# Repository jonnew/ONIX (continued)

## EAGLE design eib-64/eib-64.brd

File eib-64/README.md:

# eib-64
64-channel electrode interface board (EIB) with electrical and optical
stimulation. Designed for small animal (e.g. mouse) tetrode electrophysiology.
Compatible with [headstage-64](../headstage-64/) and small shuttle-drives.

## Gerber Files
{% include gerber_layers.md %}

## Bill of Materials
The BOM is located on [this google
sheet](https://docs.google.com/spreadsheets/d/1F-KWcdvH_63iXjZf0cgCfDiFX6XXW3qw6rlR8DZrFpQ/edit#gid=1934583654).

## Pinout
The EIB pinout (ADC input mapping, stimulation connections, etc) is located on [this google sheet](https://docs.google.com/spreadsheets/d/11wRDYOqHN5lPb03yUdfXfK0zvaDYsVetplaNK-R90Gg/edit#gid=0)

## Tetrode Connectorization
This EIB uses Neuralynx ["small" gold pins](https://neuralynx.com/hardware/small-eib-pins) to attach tetrode wires. Usage instructions are provided in the [Neuralynx EIB pin Manual](https://neuralynx.com/documents/EIB%20Pins%20Manual.pdf).

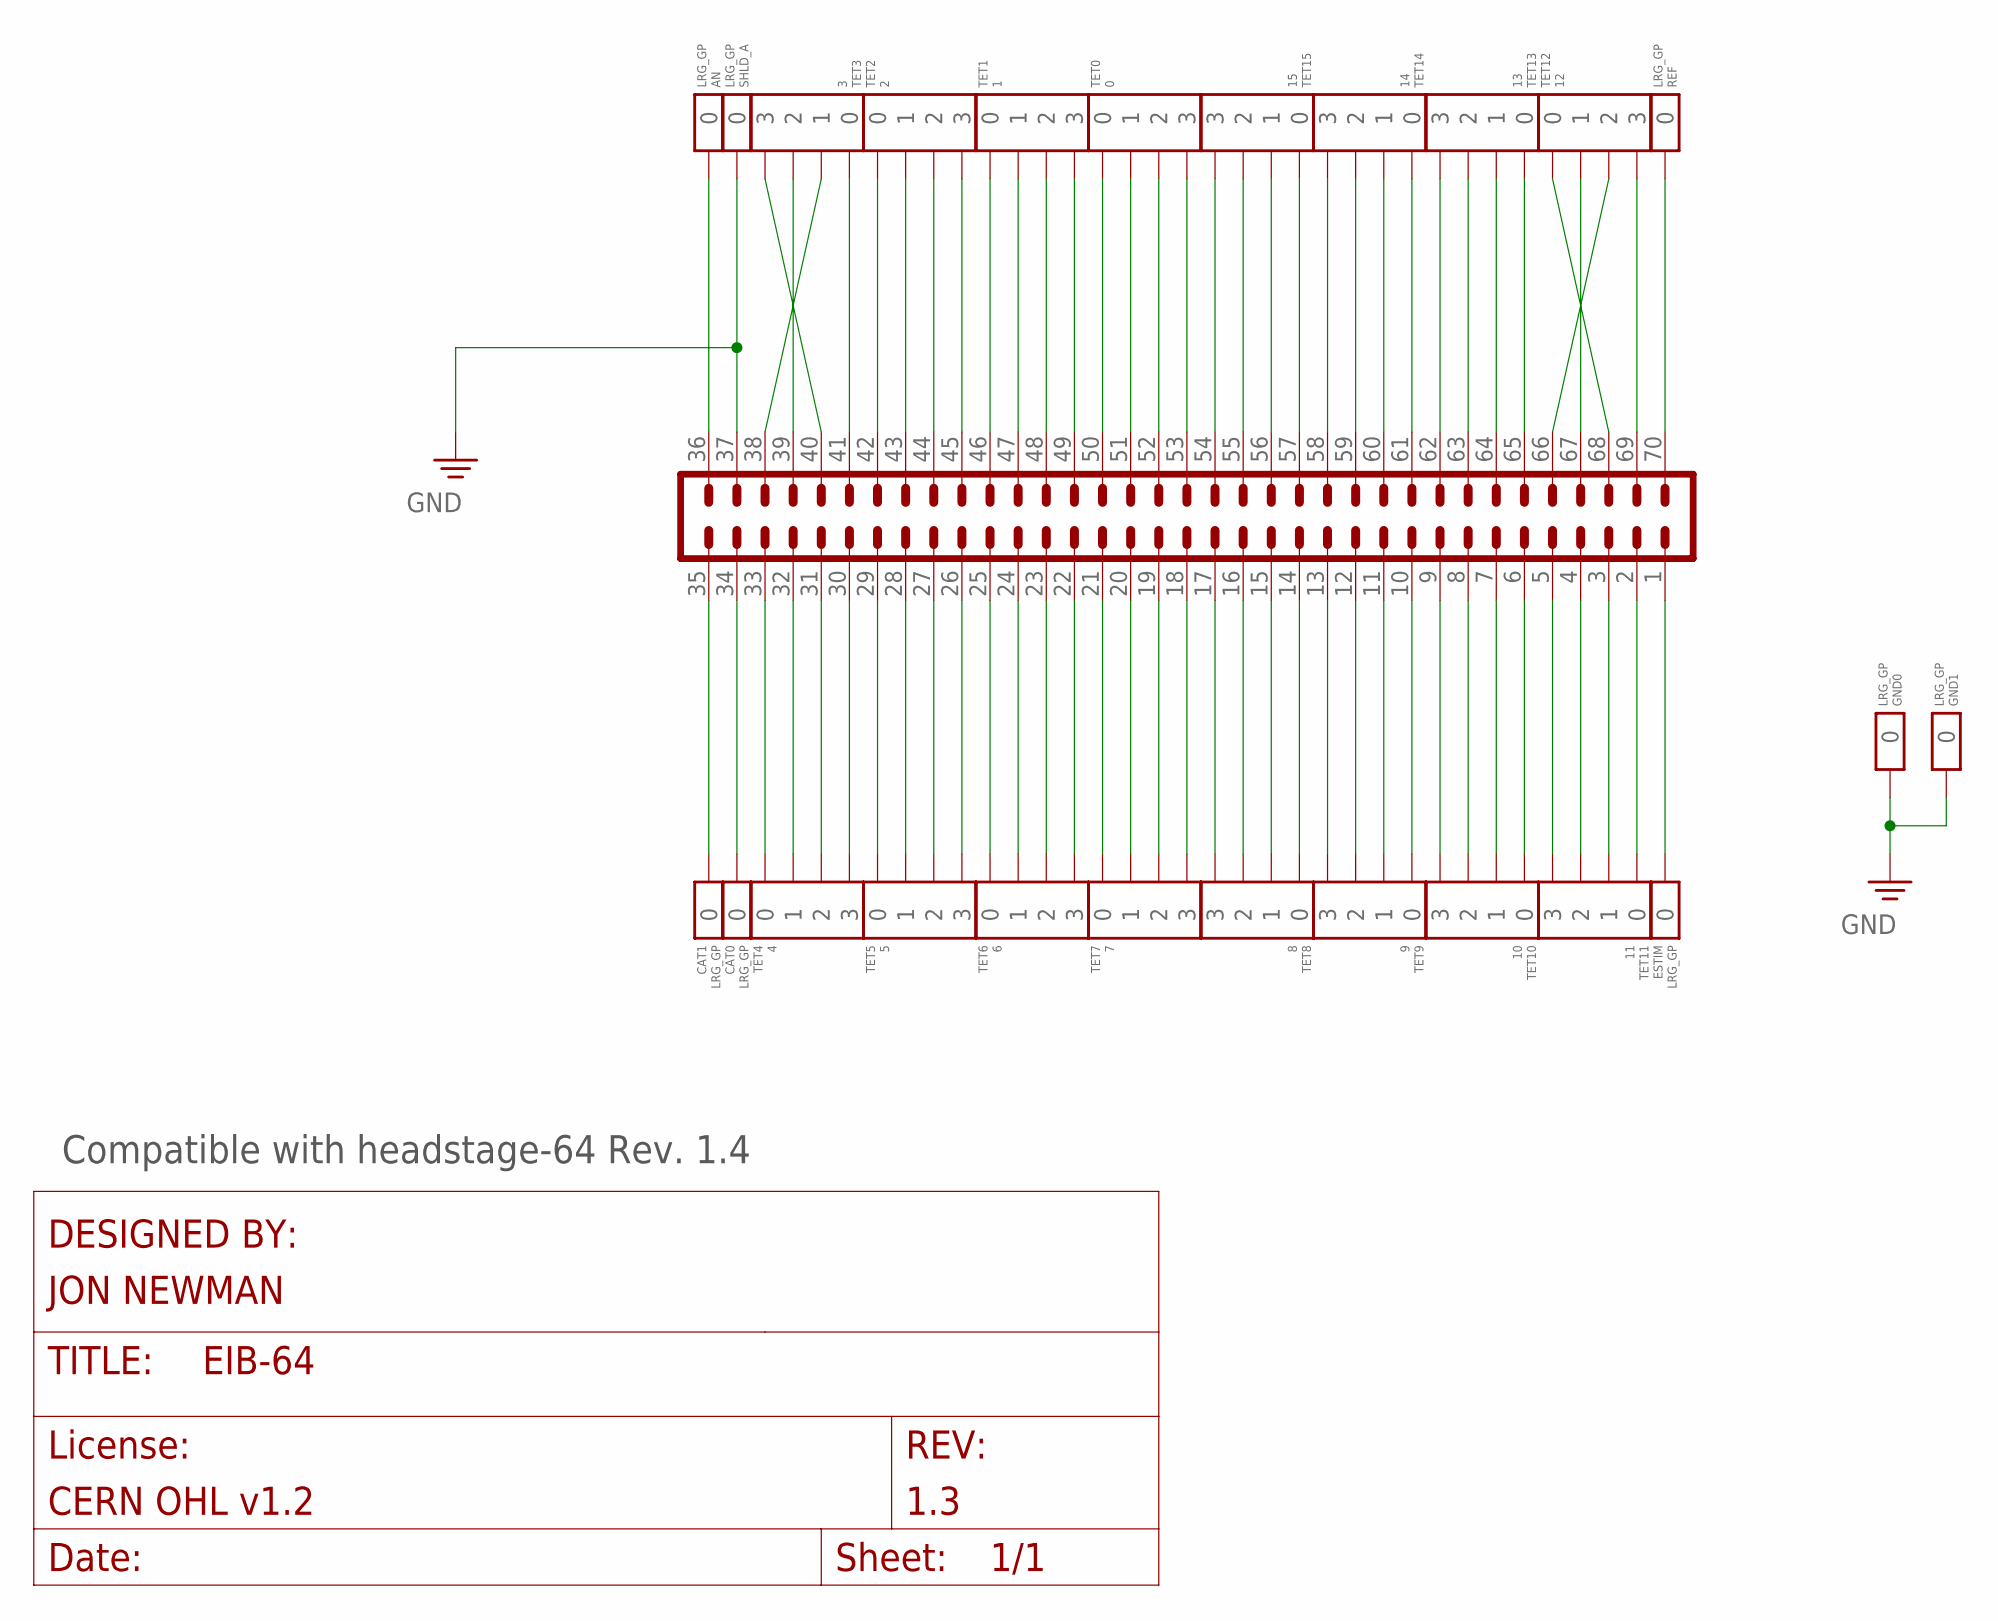
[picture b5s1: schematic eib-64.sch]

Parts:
AN: LRG_GP; GOLDPIN_0.5ID_0.7OD
CAT0, CAT1: LRG_GP; GOLDPIN_0.5ID_0.7OD
ESTIM: LRG_GP; GOLDPIN_0.5ID_0.7OD
GND0, GND1: LRG_GP; GOLDPIN_0.5ID_0.7OD
J1: DF40-REC; DF40-70REC
REF: LRG_GP; GOLDPIN_0.5ID_0.7OD
SHLD_A: LRG_GP; GOLDPIN_0.5ID_0.7OD
TET0: 0; TETRODE_0.3ID_LINEAR_MOUSE
TET1: 1; TETRODE_0.3ID_LINEAR_MOUSE
TET2: 2; TETRODE_0.3ID_LINEAR_MOUSE
TET3: 3; TETRODE_0.3ID_LINEAR_MOUSE
TET4: 4; TETRODE_0.3ID_LINEAR_MOUSE
TET5: 5; TETRODE_0.3ID_LINEAR_MOUSE
TET6: 6; TETRODE_0.3ID_LINEAR_MOUSE
TET7: 7; TETRODE_0.3ID_LINEAR_MOUSE
TET8: 8; TETRODE_0.3ID_LINEAR_MOUSE
TET9: 9; TETRODE_0.3ID_LINEAR_MOUSE
TET10: 10; TETRODE_0.3ID_LINEAR_MOUSE
TET11: 11; TETRODE_0.3ID_LINEAR_MOUSE
TET12: 12; TETRODE_0.3ID_LINEAR_MOUSE
TET13: 13; TETRODE_0.3ID_LINEAR_MOUSE
TET14: 14; TETRODE_0.3ID_LINEAR_MOUSE
TET15: 15; TETRODE_0.3ID_LINEAR_MOUSE

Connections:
AN: AN.P$1, J1.36
CAT0: CAT0.P$1, J1.34
CAT1: CAT1.P$1, J1.35
ESTIM: ESTIM.P$1, J1.1
GND: GND0.P$1, GND1.P$1, J1.37, SHLD_A.P$1
unnamed: J1.69, TET12.3
unnamed: J1.66, TET12.2
unnamed: J1.67, TET12.1
unnamed: J1.68, TET12.0
unnamed: J1.65, TET13.0
unnamed: J1.64, TET13.1
unnamed: J1.63, TET13.2
unnamed: J1.62, TET13.3
unnamed: J1.61, TET14.0
unnamed: J1.60, TET14.1
unnamed: J1.59, TET14.2
unnamed: J1.58, TET14.3
unnamed: J1.57, TET15.0
unnamed: J1.56, TET15.1
unnamed: J1.55, TET15.2
unnamed: J1.54, TET15.3
unnamed: J1.53, TET0.3
unnamed: J1.52, TET0.2
unnamed: J1.51, TET0.1
unnamed: J1.50, TET0.0
unnamed: J1.49, TET1.3
unnamed: J1.48, TET1.2
unnamed: J1.47, TET1.1
unnamed: J1.46, TET1.0
unnamed: J1.45, TET2.3
unnamed: J1.44, TET2.2
unnamed: J1.43, TET2.1
unnamed: J1.42, TET2.0
unnamed: J1.41, TET3.0
unnamed: J1.40, TET3.3
unnamed: J1.39, TET3.2
unnamed: J1.38, TET3.1
unnamed: J1.5, TET11.3
unnamed: J1.4, TET11.2
unnamed: J1.3, TET11.1
unnamed: J1.2, TET11.0
unnamed: J1.33, TET4.0
unnamed: J1.32, TET4.1
unnamed: J1.31, TET4.2
unnamed: J1.30, TET4.3
unnamed: J1.29, TET5.0
unnamed: J1.28, TET5.1
unnamed: J1.27, TET5.2
unnamed: J1.26, TET5.3
unnamed: J1.25, TET6.0
unnamed: J1.24, TET6.1
unnamed: J1.23, TET6.2
unnamed: J1.22, TET6.3
unnamed: J1.21, TET7.0
unnamed: J1.20, TET7.1
unnamed: J1.19, TET7.2
unnamed: J1.18, TET7.3
unnamed: J1.17, TET8.3
unnamed: J1.16, TET8.2
unnamed: J1.15, TET8.1
unnamed: J1.14, TET8.0
unnamed: J1.13, TET9.3
unnamed: J1.12, TET9.2
unnamed: J1.11, TET9.1
unnamed: J1.10, TET9.0
unnamed: J1.9, TET10.3
unnamed: J1.8, TET10.2
unnamed: J1.7, TET10.1
unnamed: J1.6, TET10.0
REF: J1.70, REF.P$1

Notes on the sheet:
Compatible with headstage-64 Rev. 1.4

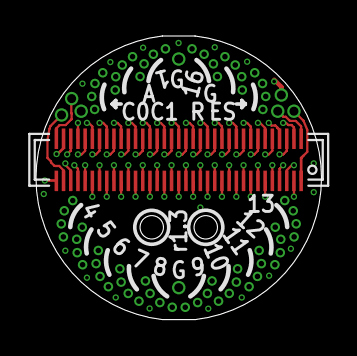
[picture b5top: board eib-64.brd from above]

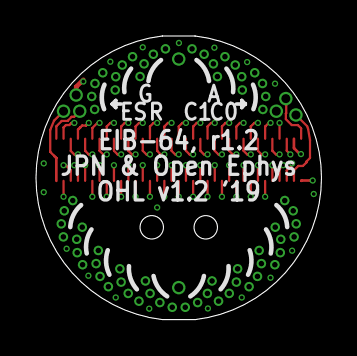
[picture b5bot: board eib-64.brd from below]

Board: 4 copper layers, 15.9 x 15.8 mm, 25 parts (8 on the bottom side), 70 nets.
